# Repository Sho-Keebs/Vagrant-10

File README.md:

# Vagrant-10

PCB for small, 10-key macropad. Compatible with **MX-style** and **Alps** switches.

## Firmware

You can find precompiled firmware inside [pc-firmware](https://github.com/Sho-Keebs/Vagrant-10/blob/master/pc-firmware/) directory or compile it from [QMK](https://github.com/qmk/qmk_firmware). It is available to configure in [QMK Configurator](https://config.qmk.fm/#/vagrant_10/LAYOUT)!

## Layout

## PCB

## Build guide

I suggest using [PyrooL's Aplpha build guide](https://github.com/PyrooL/Alpha) as those keyboards are built with the same components.

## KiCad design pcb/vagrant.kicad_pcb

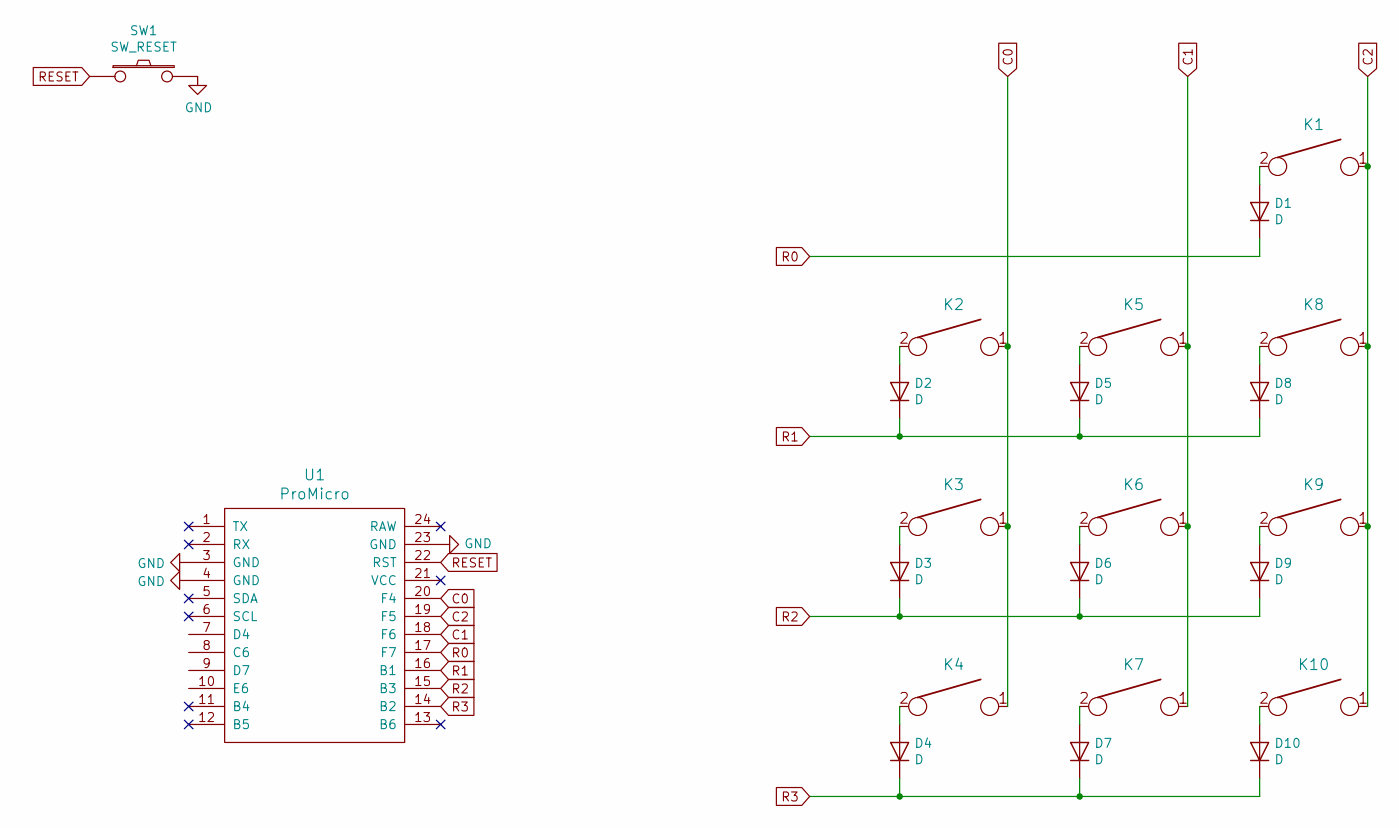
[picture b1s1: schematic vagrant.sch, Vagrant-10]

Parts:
D1, D2, D3, D4, D5, D6, D7, D8, D9, D10: D; D_DO-35_SOD27_P7.62mm_Horizontal
K1: KEYSW; MX-2U-NoLED
K2, K3, K4, K5, K6, K7, K8, K9, K10: KEYSW; MX-1U-NoLED
SW1: SW_RESET; SW_PUSH_6mm
U1: ProMicro

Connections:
C0: K2.1, K3.1, K4.1, U1.20 (F4)
C1: K5.1, K6.1, K7.1, U1.18 (F6)
C2: K1.1, K8.1, K9.1, K10.1, U1.19 (F5)
GND: SW1.2, U1.3 (GND), U1.4 (GND), U1.23 (GND)
unnamed: D1.2 (A), K1.2
unnamed: D2.2 (A), K2.2
unnamed: D3.2 (A), K3.2
unnamed: D4.2 (A), K4.2
unnamed: D5.2 (A), K5.2
unnamed: D6.2 (A), K6.2
unnamed: D7.2 (A), K7.2
unnamed: D8.2 (A), K8.2
unnamed: D9.2 (A), K9.2
unnamed: D10.2 (A), K10.2
R0: D1.1 (K), U1.17 (F7)
R1: D2.1 (K), D5.1 (K), D8.1 (K), U1.16 (B1)
R2: D3.1 (K), D6.1 (K), D9.1 (K), U1.15 (B3)
R3: D4.1 (K), D7.1 (K), D10.1 (K), U1.14 (B2)
RESET: SW1.1, U1.22 (RST)

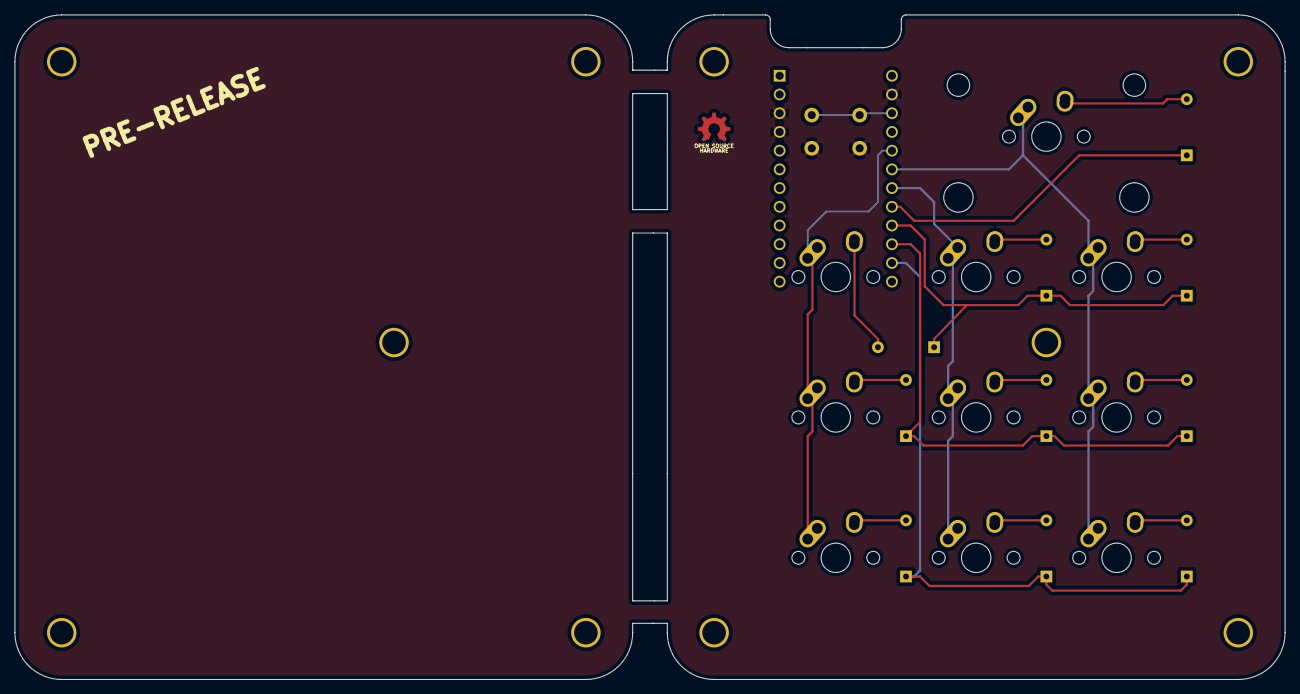
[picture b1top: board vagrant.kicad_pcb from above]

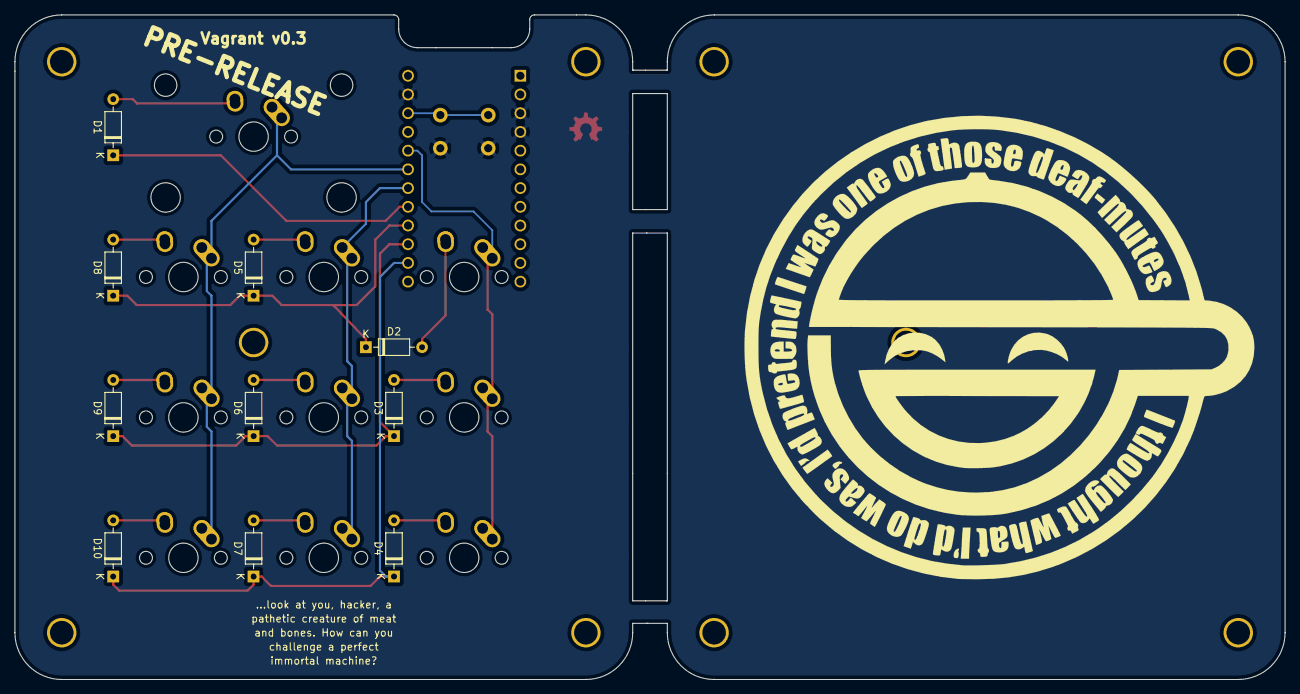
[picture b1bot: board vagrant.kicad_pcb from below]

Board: 2 copper layers, 172.3 x 90.2 mm, 32 parts (10 on the bottom side), 19 nets.

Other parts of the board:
HOLE_M3, HOLE_M3#2, HOLE_M3#3, HOLE_M3#4, HOLE_M3#5, HOLE_M3#6, HOLE_M3#7, HOLE_M3#8, HOLE_M3#9, HOLE_M3#10: VAL**; HOLE_M3

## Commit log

2020-02-17 Designed
2020-02-17 added Readme
2020-02-19 minor changes on silk
2020-03-08 Fixup space between parts
2020-08-15 Images :)
2020-08-16 Added firmware
2022-10-27 docs: updated readme
